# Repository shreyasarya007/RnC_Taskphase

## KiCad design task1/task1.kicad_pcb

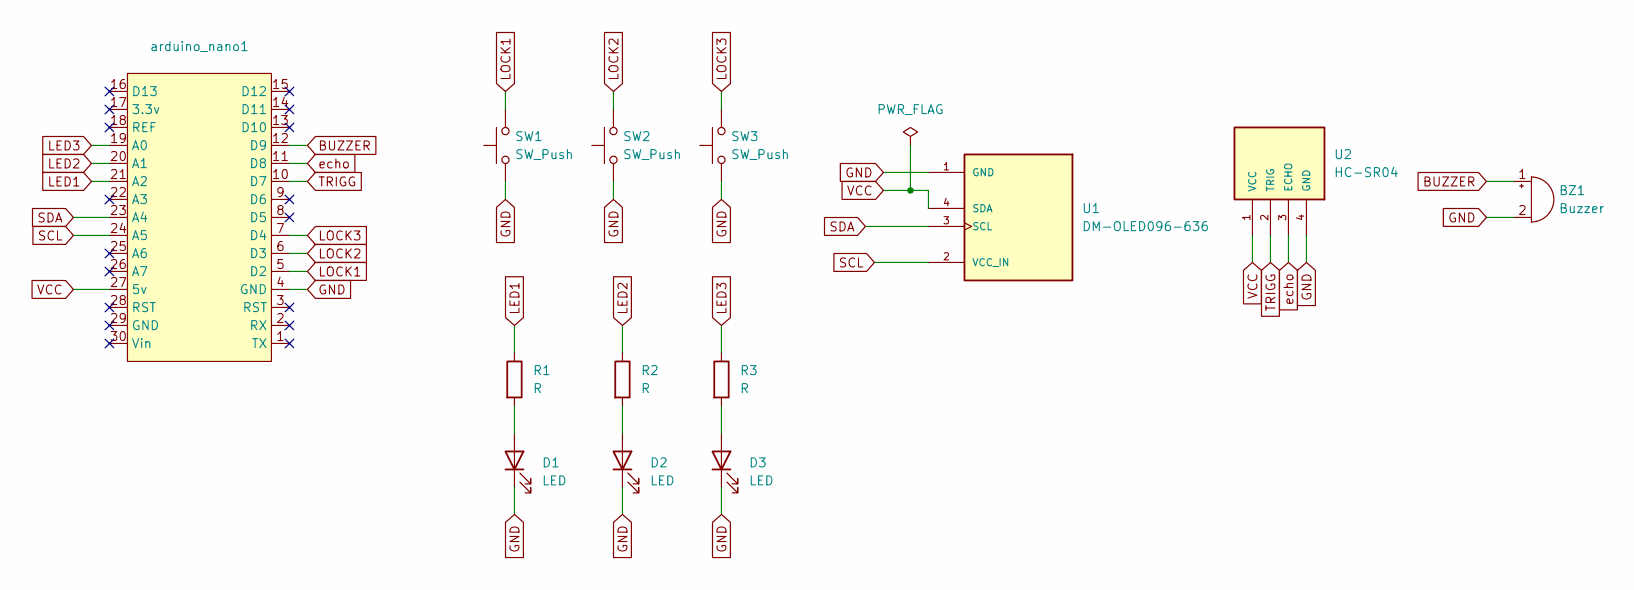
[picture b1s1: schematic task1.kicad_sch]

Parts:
BZ1: Buzzer; Buzzer_12x9.5RM7.6
D1, D2, D3: LED; LED_D1.8mm_W1.8mm_H2.4mm_Horizontal_O1.27mm_Z1.6mm
R1, R2, R3: R; R_Axial_DIN0207_L6.3mm_D2.5mm_P7.62mm_Horizontal
SW1, SW2, SW3: SW_Push; SW_PUSH_6mm_H8mm
U1: DM-OLED096-636; I2C_LCD(OLED); PARTREV 2018-09-10
U2: HC-SR04
arduino_nano1: arduino nano footprint

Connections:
BUZZER: BZ1.1 (+), arduino_nano1.12 (D9)
GND: BZ1.2 (-), D1.1 (K), D2.1 (K), D3.1 (K), SW1.1, SW2.1, SW3.1, U1.1 (GND), U2.4 (GND), arduino_nano1.4 (GND)
LED1: R1.1, arduino_nano1.21 (A2)
LED2: R2.1, arduino_nano1.20 (A1)
LED3: R3.1, arduino_nano1.19 (A0)
LOCK1: SW1.2, arduino_nano1.5 (D2)
LOCK2: SW2.2, arduino_nano1.6 (D3)
LOCK3: SW3.2, arduino_nano1.7 (D4)
unnamed: D1.2 (A), R1.2
unnamed: D2.2 (A), R2.2
unnamed: D3.2 (A), R3.2
SCL: U1.2 (VCC_IN), arduino_nano1.24 (A5)
SDA: U1.3 (SCL), arduino_nano1.23 (A4)
TRIGG: U2.2 (TRIG), arduino_nano1.10 (D7)
VCC: U1.4 (SDA), U2.1 (VCC), arduino_nano1.27 (5v)
echo: U2.3 (ECHO), arduino_nano1.11 (D8)

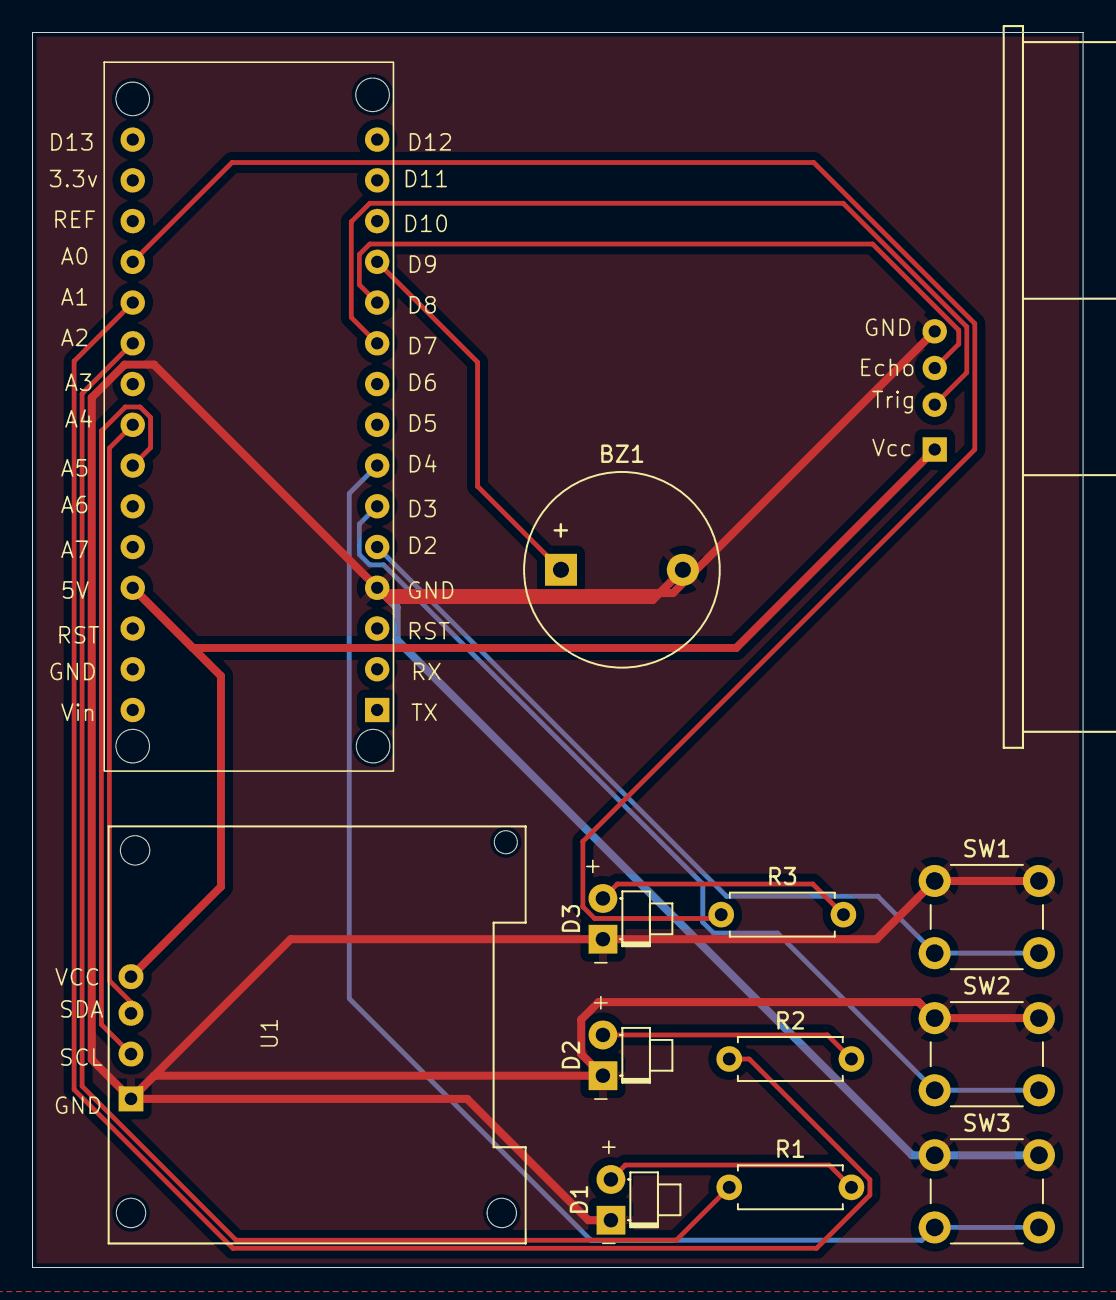
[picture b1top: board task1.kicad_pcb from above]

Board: 2 copper layers, 65.5 x 77.0 mm, 13 parts (0 on the bottom side), 16 nets.
